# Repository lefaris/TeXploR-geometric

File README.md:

# TeXploR-geometric

This repository contains the code, simulation, and design files for the Tensegrity eXploratory Robot (TeXploR), a novel curved-link tensegrity robot with internal mass shifting and multi-point contact locomotion.  This is supplemental for **Geometric Static Modeling Framework for Piecewise-Continuous Curved-Link Multi Point-of-Contact Tensegrity Robots** published in IEEE RA-L in 2024 and presented at IEEE ICRA 2025.

---

## Overview

TeXploR is a unique tensegrity robot comprised of two semi-circular curved links held together by a continuous elastic cable in 12 prestressed segments. The robot achieves locomotion through internal mass shifting along each link, enabling efficient rolling with enhanced stability (e.g., tip-over resistance on inclines).  Our work presents a geometric modeling framework to describe the hybrid system behavior of TeXploR.

### Key Contributions

- **Curved-Link Tensegrity Design**: Two semi-circular links connected with an elastic cable to maintain structural integrity
- **Internal Actuation**: Internal masses shift along GT2 timing belts for locomotion with ~1:1 (431g:427g) arc to shifting mass ratio
- **Geometric Modeling**: Piecewise continuous approach models the holonomic constraints and pivot points
- **Four-State Hybrid System**: Rolling locomotion through state transitions between ground contact points

---

## Demos

### Internal Mass Shifting

### Rolling Locomotion

### Four-State Transition

---

## Repository Structure

```
TeXploR-geometric/
├── design files/           # CAD files for TeXploR components
│   └── PCBs/               # PCB .brd and .sch files
├── experiments/            # C++ test scripts and experimental data
│   ├── lab_cam_view/       # Overhead view of experiments
│   └── Lauren_cam_view/    # Side view of experiments
├── figure generation/      # MATLAB scripts for generating figures
│   └── simulation figures/ # 4-state static eequilibrium simulations
├── gazebo/                 # Gazebo simulation files and launch scripts
│   ├── custom_worlds/      # World and Launch files
│   │   └── ShelbyQuad/     # DAE and texture files for custom world
│   └── sphericon_test2/    # URDF, launch, config, and mesh files
│       ├── config/
│       ├── launch/
│       ├── meshes/
│       └── urdf/
├── geometric modeling/     # Core geometric modeling MATLAB code
│   └── FixingNonvalidVals  # Checking for nonpositive force values
└── media/                  # Demonstration videos and media
```

---
## Getting Started

### Prerequisites

- MATLAB R2020b or later
- Arduino IDE (for hardware deployment)
- Gazebo (optional, for world simulation)

### Installation

```bash
# Clone the repository
git clone https://github.com/lefaris/TeXploR-geometric.git
cd TeXploR-geometric

# Set up MATLAB path
# Add all subdirectories to your MATLAB path
```

### Running the Geometric Model

```matlab
% Open MATLAB and navigate to geometric modeling directory
cd 'geometric modeling/FixingNonvalidVals'

% For theta1, theta2 input values, find the corresponding
% transformation matrix Tsb and zb, and plot the positions
example = TExploRStatics(0,90)
staticPoses = example.computeStaticPoses()

% You can also access other properties of the static class
case2_Tsb_1 = staticPoses.Case2(1).Tsb
```

### Running Gazebo Simulations (work in progress)

```bash
# Launch Gazebo simulation
cd gazebo
roslaunch sphericon_test2 gazebo.launch
```
---

## Key Results

The MAE between the simulated model and experimental prototype is only 4.36°.

---

## Citation

If you use this work in your research, please cite:

```bibtex
@article{texplor2024,
  title={Geometric Static Modeling Framework for Piecewise-Continuous Curved-Link Multi Point-of-Contact Tensegrity Robots},
  author={Ervin, Lauren and Vikas, Vishesh},
  journal={IEEE Robotics and Automation Letters},
  year={2024},
  volume={9},
  number={12},
  pages={11066-11073},
  doi={10.1109/LRA.2024.3486199}
}
```

**arXiv preprint:** [arxiv:2407.01865](https://arxiv.org/abs/2407.01865)

---
## Updates

- **January 2026:** Updated [TeXploRV2](https://github.com/lefaris/TeXploR-quasi) paper accepted to IEEE ICRA 2026
- **May 2025:** Paper presented at IEEE ICRA 2025
- **December 2024:** Paper published in IEEE RA-L
- **October 2024:** Paper accepted to IEEE RA-L

---
## License

This project is released for academic and research purposes.

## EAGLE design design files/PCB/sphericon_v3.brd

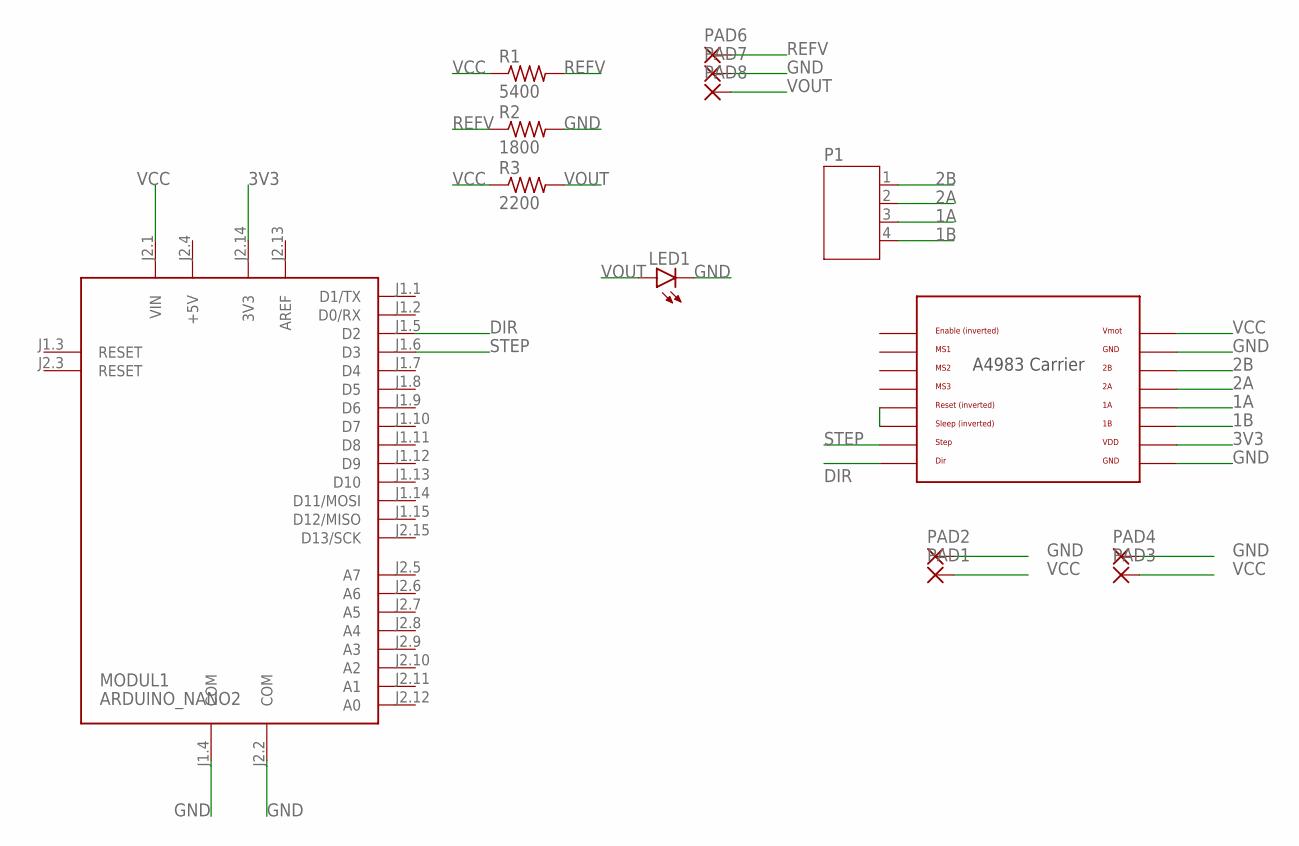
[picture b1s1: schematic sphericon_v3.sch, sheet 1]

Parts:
LED1: LED3MM
MODUL1: ARDUINO_NANO2
P1: JST-PH4
PAD1, PAD2, PAD3, PAD4, PAD6, PAD7, PAD8: 1,6/0,8
R1: 5400; 0204V
R2: 1800; 0204V
R3: 2200; 0204V
U$6: POLOLU_A4983CARRIER; A4983CARRIER

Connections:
1A: P1.3, U$6.1A
1B: P1.4, U$6.1B
2A: P1.2, U$6.2A
2B: P1.1, U$6.2B
3V3: MODUL1.J2.14 (3V3), U$6.VDD
+5V: MODUL1.J2.4 (+5V)
AREF: MODUL1.J2.13 (AREF)
DIR: MODUL1.J1.5 (D2), U$6.DIR
GND: LED1.K (C), MODUL1.J1.4 (COM), MODUL1.J2.2 (COM), PAD2.1, PAD4.1, PAD7.1, R2.2, U$6.GND, U$6.GND@0 (GND)
unnamed: U$6.RST, U$6.SLP (SLEEP)
REFV: PAD6.1, R1.2, R2.1
STEP: MODUL1.J1.6 (D3), U$6.STEP
VCC: MODUL1.J2.1 (VIN), PAD1.1, PAD3.1, R1.1, R3.1, U$6.VMOT
VOUT: LED1.A, PAD8.1, R3.2

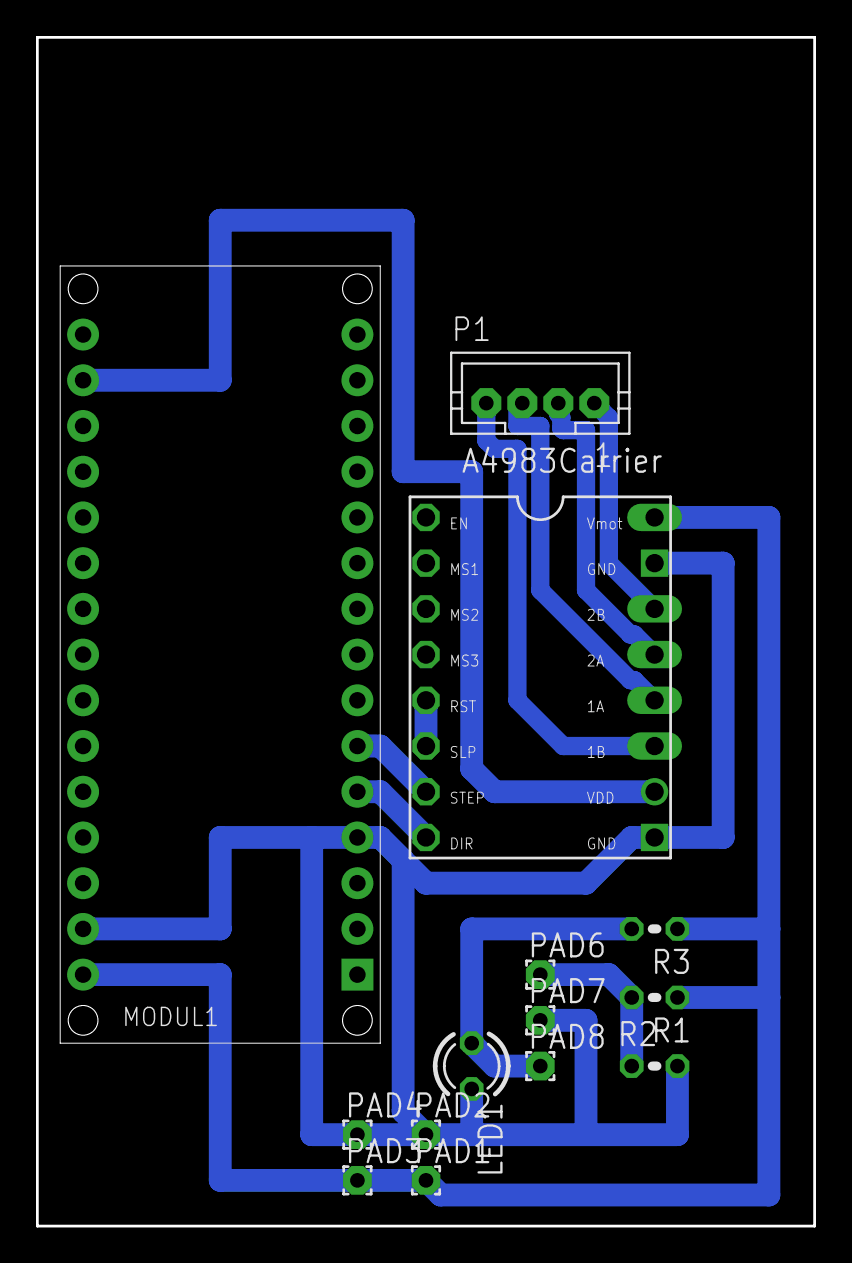
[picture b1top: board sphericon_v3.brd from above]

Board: 2 copper layers, 43.2 x 66.0 mm, 14 parts (0 on the bottom side), 12 nets.

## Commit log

2026-02-11 reorganization, Gazebo, PCBs, experiments
2026-02-11 Remove duplicate entries in updates section
2026-02-11 Fix indentation in README
